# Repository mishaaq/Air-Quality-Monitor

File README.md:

# Air-Quality-Monitor
Sketch for Z-Uno based air quality monitor (Z-Wave enabled) based on Z-Uno board and PMS5003T air quality sensor. Powered with 2 AA batteries.

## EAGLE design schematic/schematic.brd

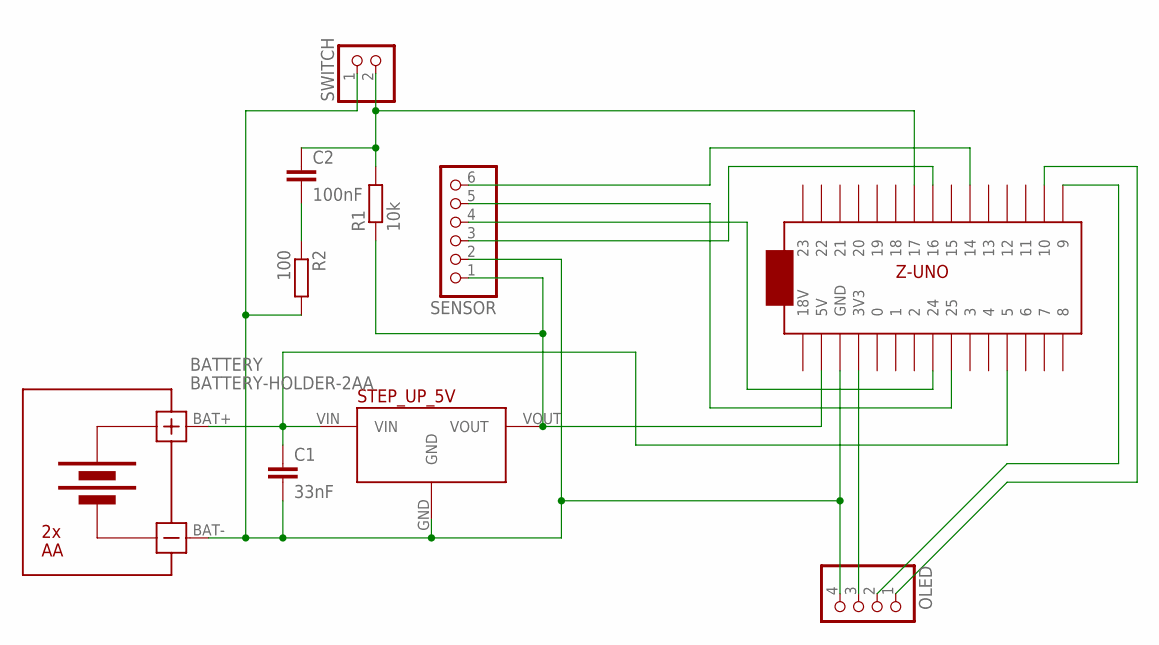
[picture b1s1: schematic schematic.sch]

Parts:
BATTERY: BATTERY-HOLDER-2AA
C1: 33nF; C025-024X044
C2: 100nF; C025-024X044
OLED: PINHD-1X4; 1X04
R1: 10k; 0204/7
R2: 100; 0204/7
SENSOR: PINHD-1X6; 1X06
STEP_UP_5V: 5V_VOLTAGE_REGULATOR
SWITCH: PINHD-1X2; 1X02
ZUNO: ZUNO

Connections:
GND: BATTERY.BAT-, C1.2, OLED.4, R2.2, SENSOR.2, STEP_UP_5V.GND, SWITCH.1, ZUNO.P$3 (GND)
INT0: C2.1, R1.2, SWITCH.2, ZUNO.P$24 (17)
RESET: SENSOR.6, ZUNO.P$21 (14)
RX: SENSOR.4, ZUNO.P$8 (24)
SCL: OLED.2, ZUNO.P$16 (9)
SDA: OLED.1, ZUNO.P$17 (10)
SET: SENSOR.3, ZUNO.P$23 (16)
SW: C2.2, R2.1
TX: SENSOR.5, ZUNO.P$9 (25)
V3V: OLED.3, ZUNO.P$4 (3V3)
V5V: R1.1, SENSOR.1, STEP_UP_5V.VOUT, ZUNO.P$2 (5V)
VIN: BATTERY.BAT+, C1.1, STEP_UP_5V.VIN, ZUNO.P$12 (5)

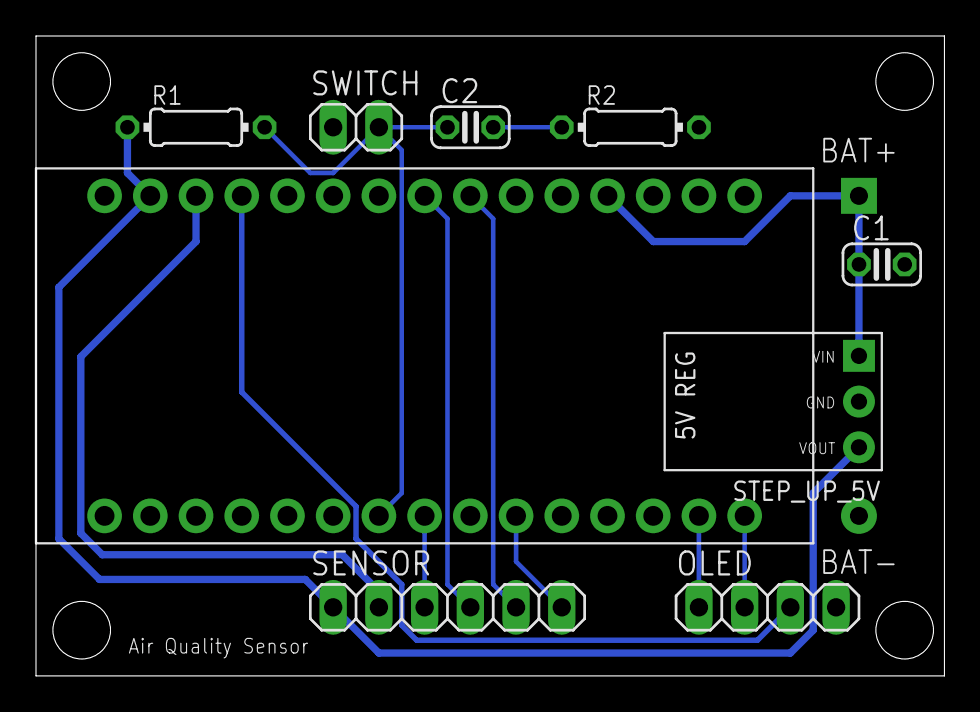
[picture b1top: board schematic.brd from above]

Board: 2 copper layers, 50.5 x 35.5 mm, 10 parts (0 on the bottom side), 12 nets.

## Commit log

2019-07-01 add eagle project

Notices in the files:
parts and their libraries:
diy-modules: Released under the Creative Commons Attribution 4.0 International License: http://creativecommons.org/licenses/by/4.0
